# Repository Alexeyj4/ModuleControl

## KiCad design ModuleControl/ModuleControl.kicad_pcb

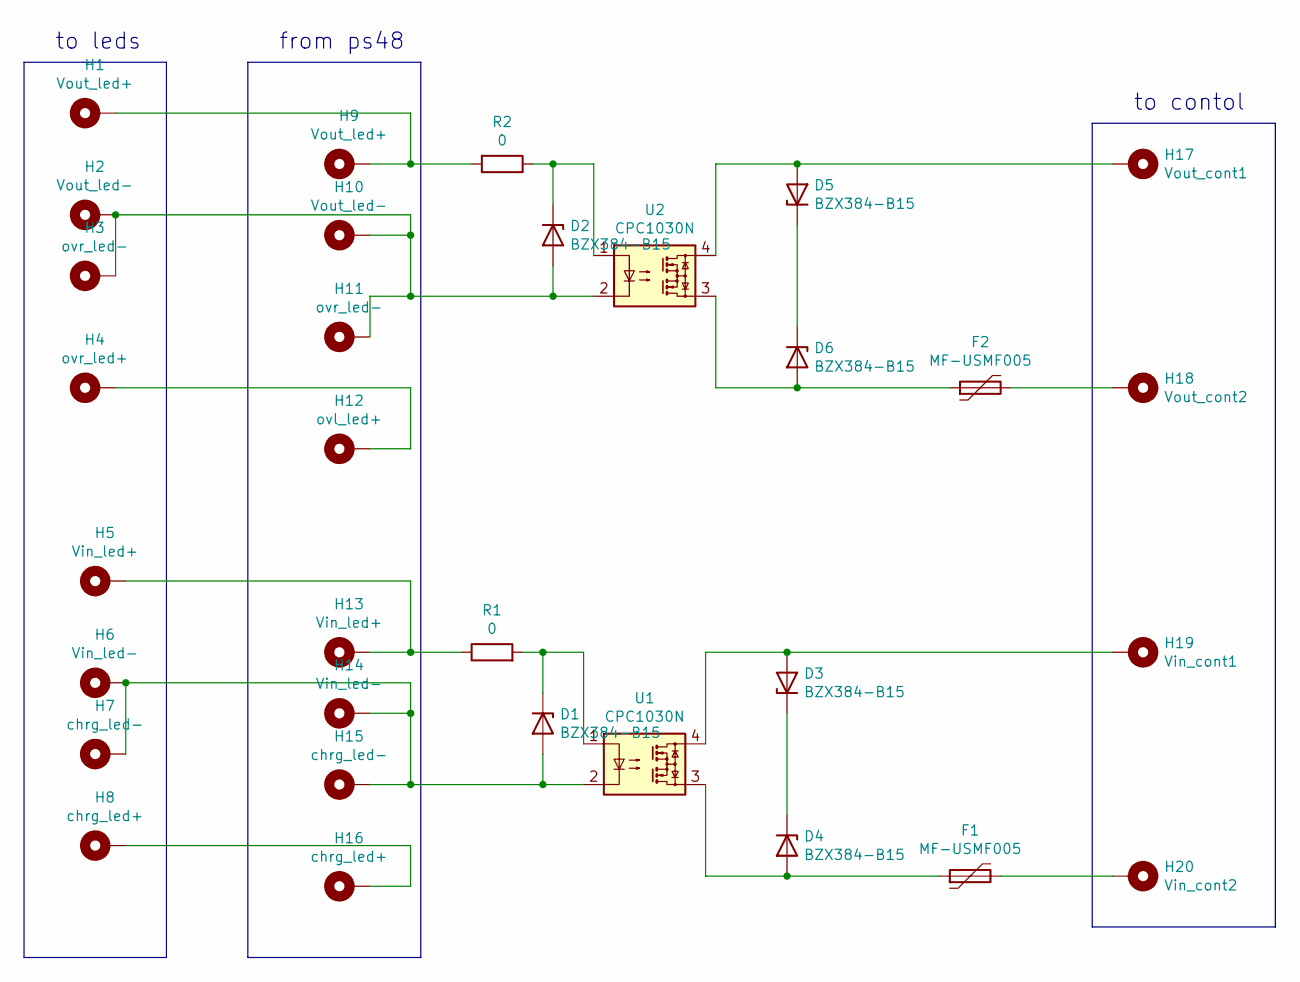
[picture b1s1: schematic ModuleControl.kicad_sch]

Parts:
D1, D2, D3, D4, D5, D6: BZX384-B15; D_SOD-323
F1, F2: MF-USMF005; R_1206_3216Metric
H1, H9: Vout_led+; SolderWirePad_1x01_SMD_1x2mm
H2, H10: Vout_led-; SolderWirePad_1x01_SMD_1x2mm
H3, H11: ovr_led-; SolderWirePad_1x01_SMD_1x2mm
H4: ovr_led+; SolderWirePad_1x01_SMD_1x2mm
H5, H13: Vin_led+; SolderWirePad_1x01_SMD_1x2mm
H6, H14: Vin_led-; SolderWirePad_1x01_SMD_1x2mm
H7, H15: chrg_led-; SolderWirePad_1x01_SMD_1x2mm
H8, H16: chrg_led+; SolderWirePad_1x01_SMD_1x2mm
H12: ovl_led+; SolderWirePad_1x01_SMD_1x2mm
H17: Vout_cont1; SolderWirePad_1x01_SMD_1x2mm
H18: Vout_cont2; SolderWirePad_1x01_SMD_1x2mm
H19: Vin_cont1; SolderWirePad_1x01_SMD_1x2mm
H20: Vin_cont2; SolderWirePad_1x01_SMD_1x2mm
R1, R2: 0; R_1206_3216Metric
U1, U2: CPC1030N; SOP-4_3.8x4.1mm_P2.54mm

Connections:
unnamed: D1.1 (K), R1.2, U1.1
unnamed: D1.2 (A), H6.1, H7.1, H14.1, H15.1, U1.2
unnamed: D2.1 (K), R2.2, U2.1
unnamed: D2.2 (A), H2.1, H3.1, H10.1, H11.1, U2.2
unnamed: D3.1 (K), D4.1 (K)
unnamed: D3.2 (A), H19.1, U1.4
unnamed: D4.2 (A), F1.1, U1.3
unnamed: D5.1 (K), D6.1 (K)
unnamed: D5.2 (A), H17.1, U2.4
unnamed: D6.2 (A), F2.1, U2.3
unnamed: F1.2, H20.1
unnamed: F2.2, H18.1
unnamed: H1.1, H9.1, R2.1
unnamed: H4.1, H12.1
unnamed: H5.1, H13.1, R1.1
unnamed: H8.1, H16.1

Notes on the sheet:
from ps48
to leds
to contol

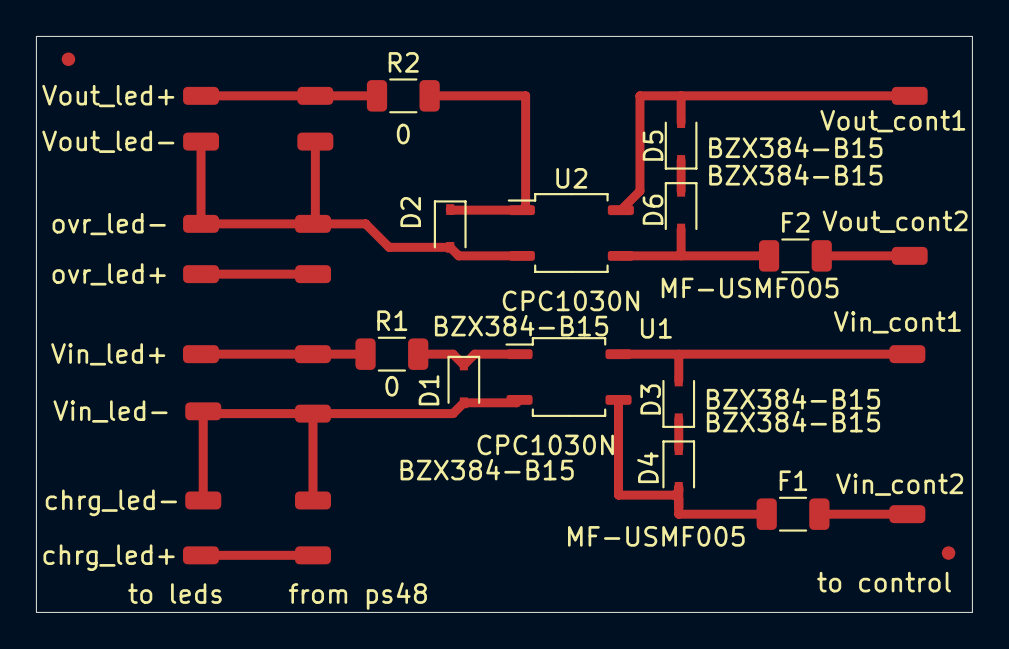
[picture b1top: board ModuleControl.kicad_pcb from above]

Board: 2 copper layers, 52.0 x 32.0 mm, 32 parts (0 on the bottom side), 16 nets.
